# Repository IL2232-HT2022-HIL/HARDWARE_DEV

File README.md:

# HARDWARE_DEV
Hardware development for the project

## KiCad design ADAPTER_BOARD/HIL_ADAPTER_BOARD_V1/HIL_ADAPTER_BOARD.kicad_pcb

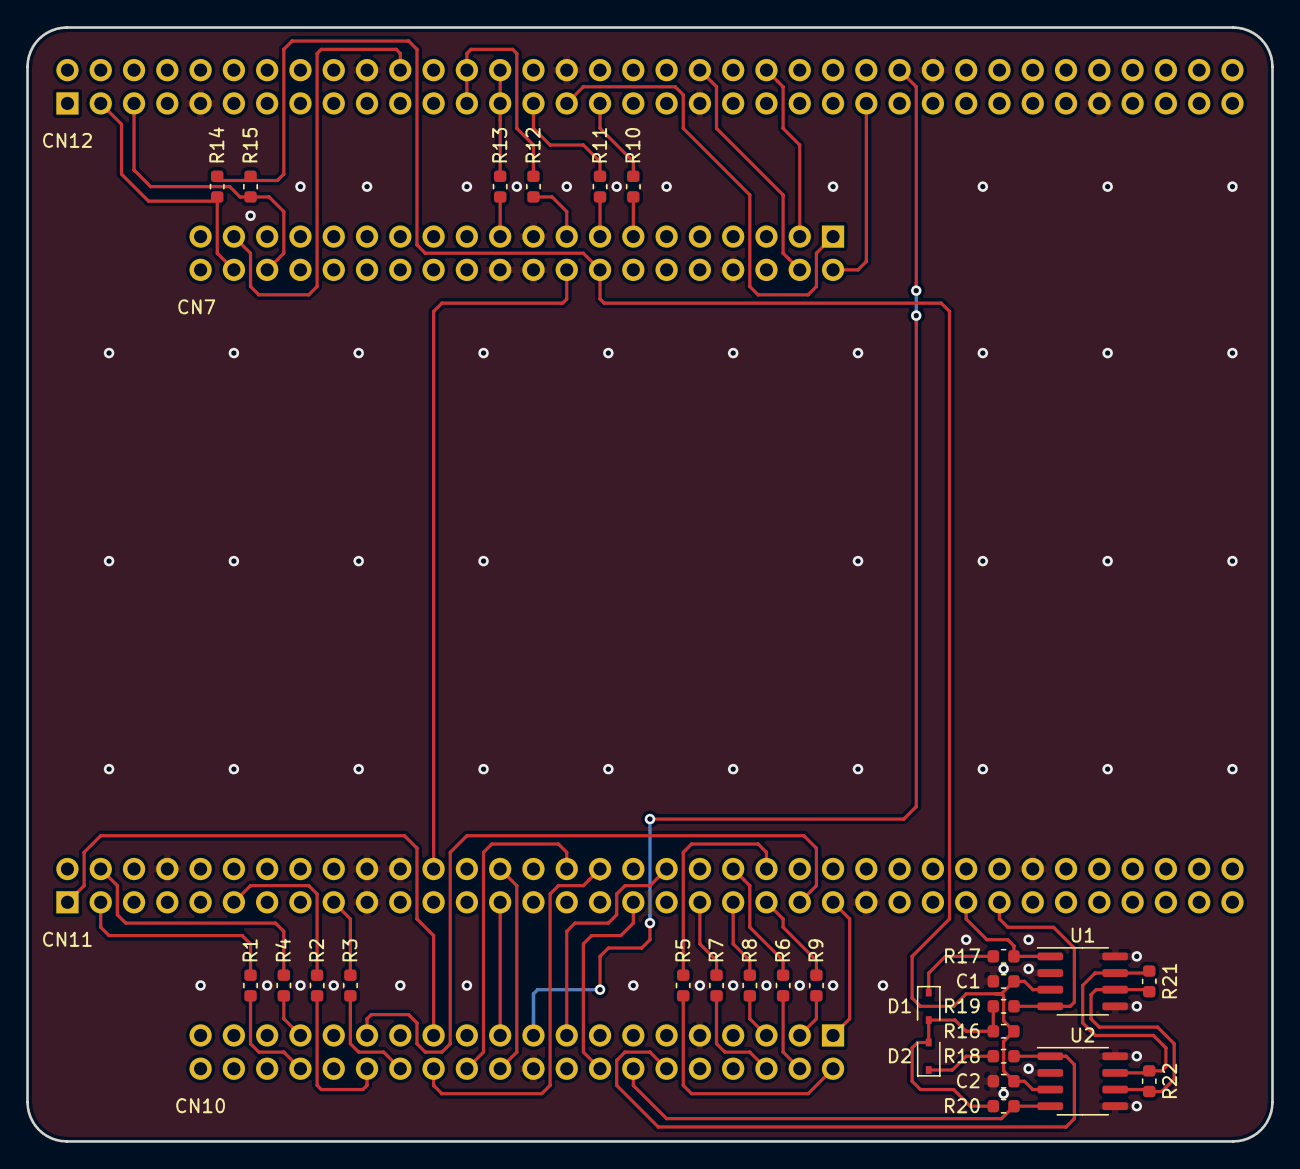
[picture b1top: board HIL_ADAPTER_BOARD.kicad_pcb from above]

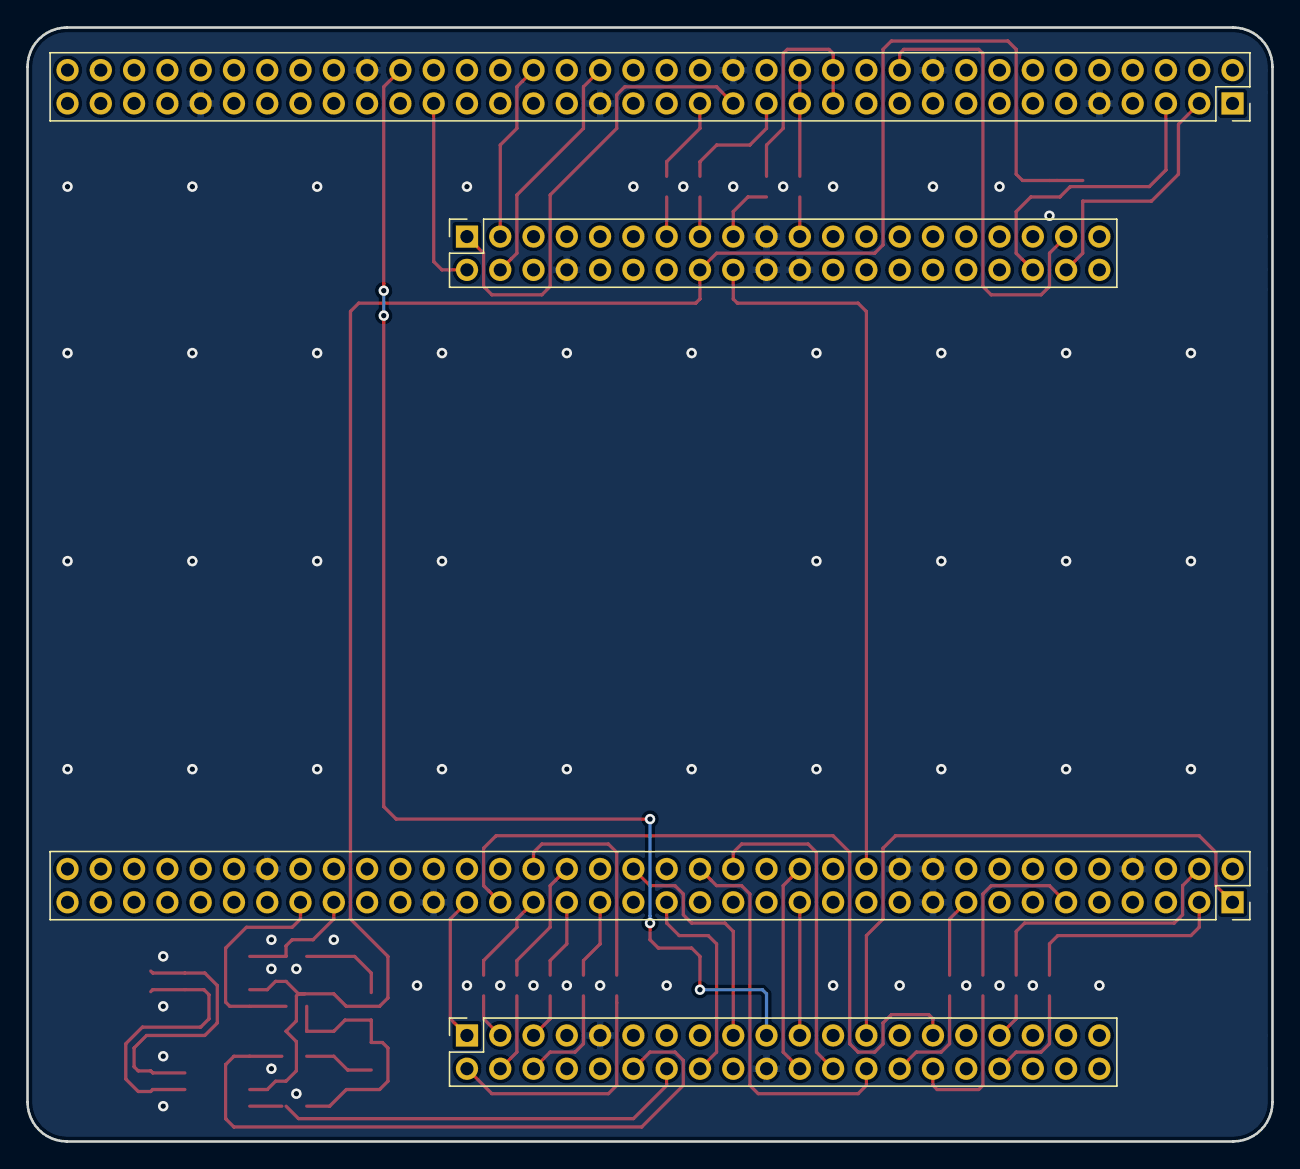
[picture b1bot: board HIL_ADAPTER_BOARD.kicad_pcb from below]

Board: 2 copper layers, 95.0 x 85.0 mm, 32 parts (4 on the bottom side), 55 nets.

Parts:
C1, C2: 100n; C_0603_1608Metric
CN7, CN10: Conn_02x20_Odd_Even; PinSocket_2x20_P2.54mm_Vertical
CN11, CN12: Conn_02x36_Odd_Even; PinSocket_2x36_P2.54mm_Vertical
D1, D2: D; D_SOD-323
R1, R2, R3, R4, R5, R6, R7, R8, R9, R10, R11, R12, R13: 1k; R_0603_1608Metric
R14, R15: 10k; R_0603_1608Metric
R16: 3k3; R_0603_1608Metric
R17, R18, R19, R20: 0; R_0603_1608Metric
R21, R22: 120; R_0603_1608Metric
U1, U2: SN65HVD233; SOIC-8_3.9x4.9mm_P1.27mm

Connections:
+3V3: C1.1, C2.1, CN7.16, R14.1, R15.1, R16.1, U1.3, U2.3
/595_DS: CN10.29, CN11.45
/595_Enable: CN10.19, CN12.52
/595_Reset: CN10.21, CN11.27
/595_SHCP: CN7.1, CN12.31
/595_STCP: CN10.16, CN11.35
/CAN_RX: CN10.14, R20.1, U2.4
/CAN_TX: CN10.12, R18.1, U2.1
/DEV_5V: CN7.18, CN11.24
/Disp_CS: CN7.2, CN12.49
/Disp_Data-Instr: CN10.1, CN11.47
/Disp_Reset: CN10.17, CN11.38
/HiL_CAN1_RX: CN11.57, R19.2, U1.4
/HiL_CAN1_TX: CN11.55, R17.2, U1.1
/HiL_I2C1_SCL: CN7.38, CN12.3, R14.2
/HiL_I2C1_SDA: CN7.36, CN12.5, R15.2
/HiL_LIS2DW12TR_Int1: CN12.33, R10.2
/HiL_LIS2DW12TR_Int2: CN12.29, R11.2
/HiL_Poti: CN10.24, CN11.32
/HiL_SPI3_MOSI: CN7.37, CN12.22
/HiL_SPI3_SCK: CN10.25, CN11.1
/HiL_SW5: CN12.25, CN12.26, R12.2
/HiL_SW7: CN12.27, CN12.28, R13.2
/HiL_TL1_Car: CN11.3, R1.2
/HiL_TL2_Car: CN11.11, R2.2
/HiL_TL3_Car: CN11.17, R3.2
/HiL_TL4_Car: CN11.4, R4.2
/HiL_UART7_RX: CN7.3, CN12.44
/HiL_UART7_TX: CN7.4, CN12.40
/HiL_USR_LED1: CN10.22, CN11.28
/HiL_USR_LED2: CN10.26, CN11.34
/HiL_button3_A: CN11.44, R5.2
/HiL_button3_B: CN11.42, R6.2
/HiL_button3_C: CN11.39, R7.2
/HiL_button3_D: CN11.41, R8.2
/HiL_button3_center: CN11.43, R9.2
/LIS2DW12TR_Int1: CN7.13, R10.1
/LIS2DW12TR_Int2: CN7.15, R11.1
/PL1_Switch: CN7.17, R12.1
/PL2_Switch: CN7.21, R13.1
/TL1_Car: CN10.34, R1.1
/TL2_Car: CN10.30, R2.1
/TL3_Car: CN10.28, R3.1
/TL4_Car: CN10.33, R4.1
/button3_A: CN10.2, R5.1
/button3_B: CN10.4, R6.1
/button3_C: CN10.6, R7.1
/button3_D: CN10.5, R8.1
/button3_center: CN10.3, R9.1
GND: C1.2, C2.2, CN7.8, CN7.19, CN7.20, CN7.22, CN10.9, CN10.20, CN11.8, CN11.19, CN11.20, CN11.22, CN11.49, CN11.60, CN12.9, CN12.20, CN12.32, CN12.39, CN12.54, CN12.63, U1.2, U1.5, U1.8, U2.2, U2.5, U2.8
unnamed: D1.1, R17.1
unnamed: D1.2, D2.2, R16.2, R19.1, R20.2
unnamed: D2.1, R18.2
unnamed: R21.1, R22.1, U1.7, U2.7
unnamed: R21.2, R22.2, U1.6, U2.6

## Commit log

2022-09-15 created an empty project for the adapter board
    see commit name
2022-09-15 push new resistor
2022-09-15 push new resistor (#2)
2022-10-18 v1 is final
2022-10-18 cleaned up the branch a bit
2022-10-19 Had to reconfigure 2 pins due to collision
2022-10-19 fixed timer issue in routing
2022-10-19 fixed timer issue
2022-10-19 Fixed comments regarding schematic
2022-10-20 added manufacturing files
2022-11-03 Merge v1 of adapter board to main (#15)
    * v1 is final
    * cleaned up the branch a bit
    * Had to reconfigure 2 pins due to collision
    * fixed timer issue in routing
    * fixed timer issue
    * Fixed comments regarding schematic
2022-11-15 fixed BOM and POS issue
    JLCPCB parsing is done with commas and not semicolons. Issue now fixed
